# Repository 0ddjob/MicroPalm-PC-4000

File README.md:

# Micro Palm Computers PC/4000
## Vale Vel Casler (founder of Micro Palm Computers)
Scrounging the web, trying to find any scrap of info I could, I stumbled upon the [name of the founder/CEO](https://archive.org/details/jobseekersguidet0000char/mode/2up?q=micropalm+dos) ... Vel Casler.  A pretty unique name so managed to find him on LinkedIn and the [university where he worked as a professor](https://www.weber.edu/wsuimages/womengenderstudies/NewsletterArchive/NL%2004-2004.PDF).  I sent him a message asking if he had any info that he could share, but discovered today (July 2025) that he [passed away about two years ago in August 2023](https://www.lindquistmortuary.com/obituaries/velton-casler).

## Summary
The PC/4000 (and PC/5000) are MS-DOS compatible handheld computers running on an [80C88](/Pictures/Micro_Palm_80C88.jpg).  The PC/4000 comes with 256KB of RAM and 512KB of "virtual disk" storage, and has a 20x8 character, 120x64 graphics capable, backlit LCD.  They run on three C-size batteries (alkaline or rechargeable NiCd).<br>  
It has a single [50-pin DD50 socket](/Pictures/Micro_Palm_DD50_interface.jpg) through which it can support the items below.<br>

According to the demo program:
- two RS232 ports (although it has four MAX232s ... ?)
- one parallel port (hi-speed, two way)
- 256KB system RAM
- two internal 256KB modules for storage
- 20x8 backlit LCD, 80x25 virtual PC screen buffer
- MicroSoft ROM DOS ver. 2.25
- IBM-PC compatible BIOS
- MS-DOS command shell

Options included:
- supertwist LCD
- removable modules (in PC/5000)
- internal modem
- bar code wand
- communication cradle
- portable printer

## [Documentation](/Documents)
Unfortunately I don't have much documentation.  I do have the [READ.ME](/Documents/README.TXT) that came on the Utilities Disk (SW10015) and a four-page leaflet [(MC10041)](/Documents/MicroPalm_PC4000_Important_Information_MC10041.pdf).
<br> <br>
It would be great to find the following:<br>
- PC/5000 User's Guide (MC10033),
- PC/5000 Technical Reference Manual (MC10034),
- MS-DOS User's Guide (MC10035), and
- MS-DOS Programmer's Reference (MC10036).

I found a [German article from 1992](http://www.cowo.de/a/1133979) - it seems to be announcing a reseller in Germany:

> With the models "PC/3000", "PC/4000" and "PC/5000" Technitron presents a family of MS-DOS PCs in pocket size. The computers come from Micro Paim Computers and are often used for meter reading, according to the Munich provider,

> The most powerful PC/5000 variant works with an 80C80 (sic) processor and a 256 KB system memory. In the PC/4000 version, the main memory is also 256 KB, a maximum of 704 KB of memory can be realized on both devices. In addition, disk storage modules with capacities of 128 KB, 256 KB, 512 KB or 1024 KB are available. All computers have a ROM bios and are compatible with IBM PCs. Applications can therefore be developed on a conventional PC and then transferred to the portable system. Programming languages such as Basic, Cobol, C, Pascal or Dbase can be used. According to Technitron, the user can make extensions to the PC/5000 model via plug-in modules. For example, an asynchronous modem, interfaces and RAM memory are offered. The LC display of the PCs works backlit, with two versions available: a standard screen for extreme temperatures (from about -30 degrees Celsius to about 65 degrees Celsius) and a more readable "Supertwist" display for areas of application where the temperature fluctuations are lower (from about -10 degrees Celsius to about 48 degrees Celsius). The display takes place in eight lines with 20 characters each. Graphics are displayed with 120x64 pixels.

> As the Munich company reports, the keyboard is protected against weather influences. The sealed buttons are positioned in such a way that they can also be operated with gloves.

## [Software](/Software)
My machine came with a [Utilities Disk](/Software/MicroPalm_Utilities_Disk_SW10015.zip)<br>

## [Firmware](/Firmware)
The machine has two ROM sockets. It appears one is for diagnostic routines and the other is the BIOS/MS-DOS.<br>
Both have been dumped.<br>
The ROMs are N27C256-2 types.<br><br>

## [Pictures](/Pictures)
Photos of the machine, including interior.

## Videos
My YouTube videos.<br>
- [Micro Palm PC/4000: Part 1](https://youtu.be/sYC32jD33a0)
- [Micro Palm PC/4000: Part 2](https://youtu.be/t-Lt_9J98sY)
- [Micro Palm PC/4000: Part 3](https://youtu.be/kz60hYqgm1A)
- [Micro Palm PC/5000: Part 1](https://youtu.be/N5rM1O0Yyvo)
- [Micro Palm PC/4000 & PC/5000: Part 5](https://youtu.be/bQWHgw3dFzg)

## DD50 Breakout Board
The DD50 interface is, as far as I know, undocumented ... well, it's documented in the missing documentation.<br>

I think it includes four serial ports at least.  Anyway, looks like I'm going to have to figure the pin out the hard way, hence the breakout board.<br>

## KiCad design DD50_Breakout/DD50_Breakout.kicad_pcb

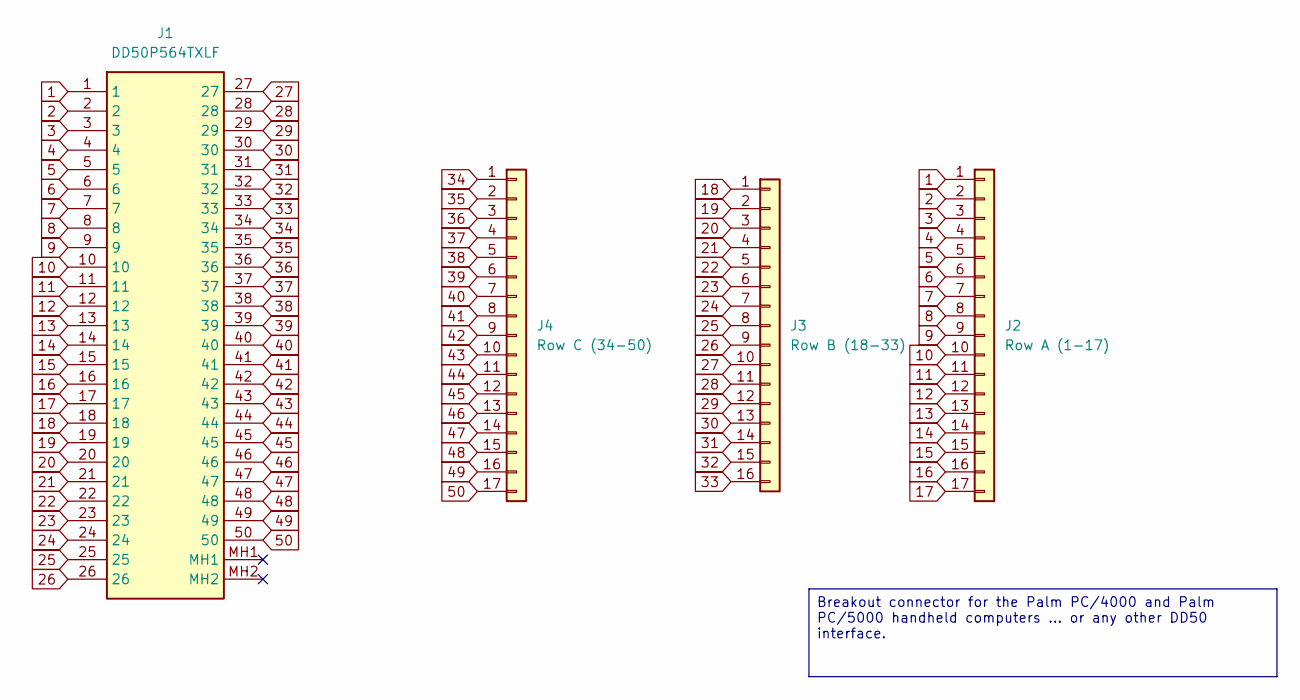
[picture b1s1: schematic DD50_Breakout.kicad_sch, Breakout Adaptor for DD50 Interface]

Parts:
J1: DD50P564TXLF; DSUB-50_Pins; Manufacturer_Part_Number DD50P564TXLF
J2: Row A (1-17); PinHeader_1x17_P2.54mm_Vertical
J3: Row B (18-33); PinHeader_1x16_P2.54mm_Vertical
J4: Row C (34-50); PinHeader_1x17_P2.54mm_Vertical

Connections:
1: J1.1, J2.1
2: J1.2, J2.2
3: J1.3, J2.3
4: J1.4, J2.4
5: J1.5, J2.5
6: J1.6, J2.6
7: J1.7, J2.7
8: J1.8, J2.8
9: J1.9, J2.9
10: J1.10, J2.10
11: J1.11, J2.11
12: J1.12, J2.12
13: J1.13, J2.13
14: J1.14, J2.14
15: J1.15, J2.15
16: J1.16, J2.16
17: J1.17, J2.17
18: J1.18, J3.1
19: J1.19, J3.2
20: J1.20, J3.3
21: J1.21, J3.4
22: J1.22, J3.5
23: J1.23, J3.6
24: J1.24, J3.7
25: J1.25, J3.8
26: J1.26, J3.9
27: J1.27, J3.10
28: J1.28, J3.11
29: J1.29, J3.12
30: J1.30, J3.13
31: J1.31, J3.14
32: J1.32, J3.15
33: J1.33, J3.16
34: J1.34, J4.1
35: J1.35, J4.2
36: J1.36, J4.3
37: J1.37, J4.4
38: J1.38, J4.5
39: J1.39, J4.6
40: J1.40, J4.7
41: J1.41, J4.8
42: J1.42, J4.9
43: J1.43, J4.10
44: J1.44, J4.11
45: J1.45, J4.12
46: J1.46, J4.13
47: J1.47, J4.14
48: J1.48, J4.15
49: J1.49, J4.16
50: J1.50, J4.17

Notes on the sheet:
Breakout connector for the Palm PC/4000 and Palm PC/5000 handheld computers ... or any other DD50 interface.

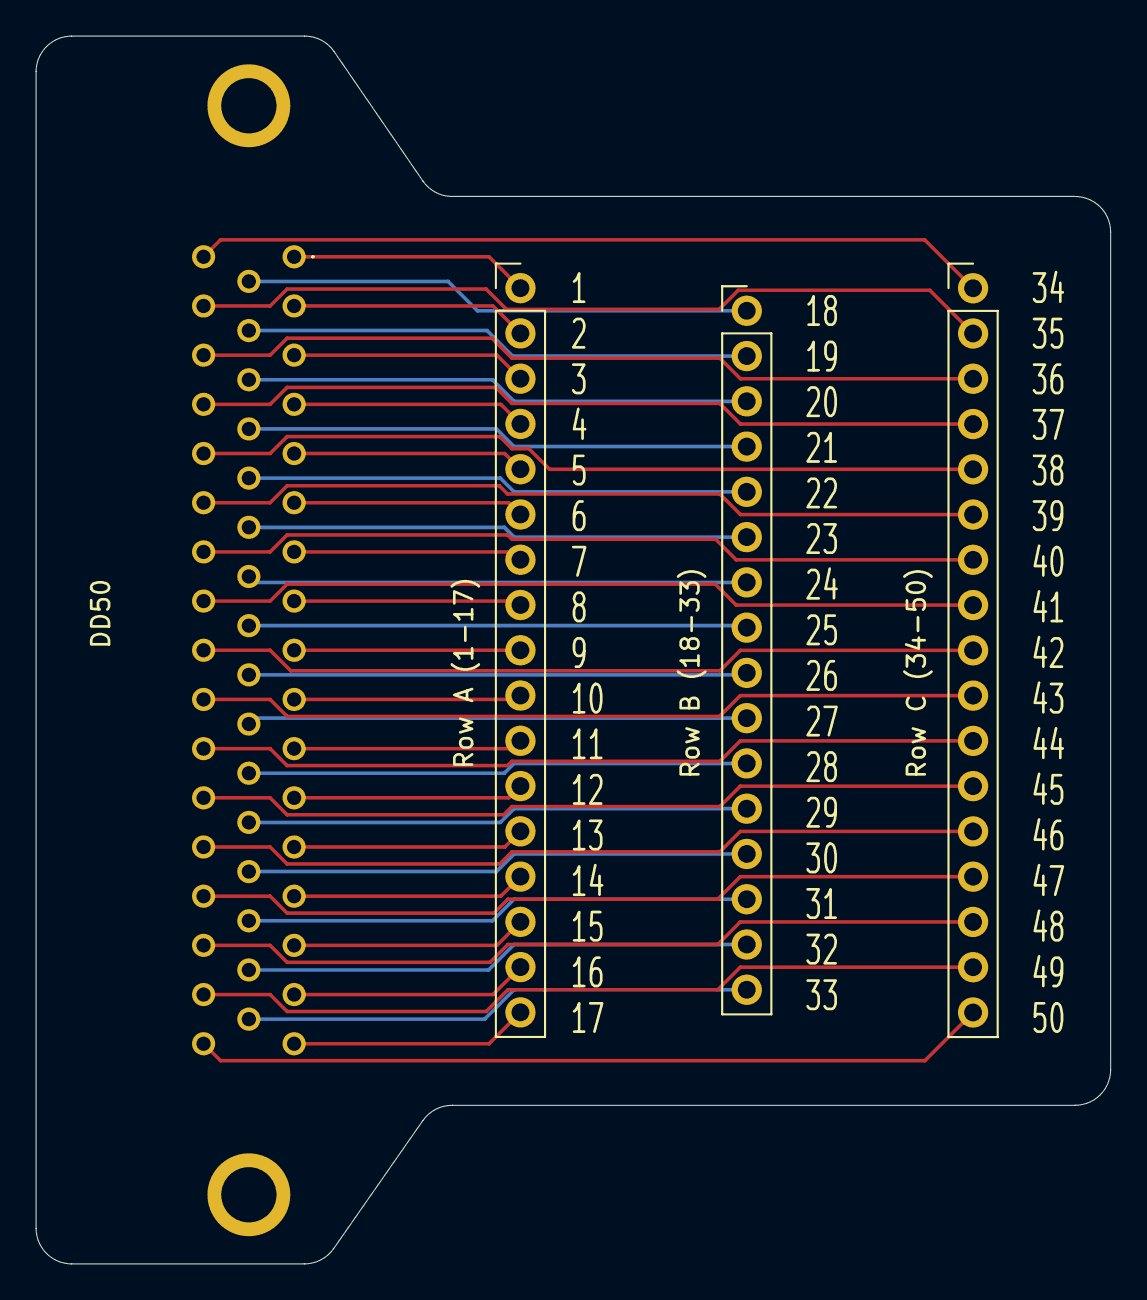
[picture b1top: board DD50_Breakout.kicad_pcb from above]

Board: 2 copper layers, 60.3 x 68.9 mm, 4 parts (0 on the bottom side), 50 nets.

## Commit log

2023-11-07 Initial commits
2023-11-07 Software
2023-11-07 More images
2023-11-07 Pictures of LSI chips
2023-11-08 Disk image of Utilities Disk (SW10015)
2023-11-09 Initial DD50 pinout
2023-11-09 Added individual files
2023-11-27 Added GE Type SC-2 Smartcoupler pinout
2023-12-16 Dumped ROMs from PC/4000 & PC/5000
2023-12-16 Firmware comments
2025-07-17 Added DD50 breakout PCB
2025-07-19 Added PNG files with transparency
2025-07-29 Further pins identified
2025-07-29 Started documenting ICs
2025-07-29 Updated IC list
